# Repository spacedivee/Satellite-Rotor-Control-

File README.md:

## *$FOR THE STARDANCE REVIEWERS$*
- In case you haven't read it through my comments already , my BOM.csv is irrelevant if you guys can **ship me a HackPad kit** +(the PCB grant). I need the exact same components as the components in the kit, so sending me my grant isn't necessary (Either way my BOM contains the same components bought individually (which just costs more than your bulk), so its a win-win for both of us if you ship a **HackPad kit**. Note: I would submit this project as a hackpad, but previous reviewers have been agaisnt that. Thank you for your understanding.

## Custom Satellite Control Interface
A custom PCB-based controller designed as a physical interface for controlling software on a computer. It can be used as a general-purpose control pad, with a focus on eventually controlling a **satellite antenna rotator** (which is another project I am building).

## Components and building materials.
* 4× MX-style buttons
* EC11E rotary encoder with push button
* 0.91" OLED display
* Seeed XIAO RP2040
* Custom KiCad PCB
* 3D-printed Onshape enclosure

## PCB+Circuit

## How It Works
The XIAO RP2040 reads the buttons and rotary encoder and sends their inputs to software running on a computer. The OLED provides feedback to the user. In my case, the OLED will display Azimuth and Elevation as they are being changed so the antenna adjustmenet can be simplified. The Encoder will be used to manually adjust the increment of the motors, such that each press will be greater or smaller, depending on the input. 
All of the information will then be sent to the XIAO, which will then sent it to my computer as keystroke data (my current method), which my antenna rotator software will then acknowledge. 

## Tools (if you were interested..?)

* **KiCad** — PCB design
* **Onshape** — enclosure design
* **Arduino/C++** — programming
* **JLCPCB** — PCB manufacturing

## Firmware
For the record, this is the only aspect of my project that was completely made by AI. The current firmware is a placeholder and I plan on writing it myself once I have built the board. I believe this is a better way
of doing things since I get to actively troubleshoot issues. I hope yall feel the same way about this ❤️.

## Bill of Materials

| Item | Component Name | Qty | Price (USD) | Notes |
| :---: | :--- | :---: | :---: | :--- |
| 1 | [Seeed XIAO RP2040](https://www.amazon.ca/dp/B0FB5BS2NX?psc=1&ref_=cm_sw_r_cp_ud_ct_R7M1Z3YGXBJXF9ZXZQDJ_10) | 1 | $19.32 | Main microcontroller |
| 2 | [1N4148 through-hole diodes](https://www.amazon.ca/dp/B099PPQ7YN?psc=1&ref_=cm_sw_r_cp_ud_ct_R7M1Z3YGXBJXF9ZXZQDJ_9) | 4 | $1.50 | Button/switch matrix |
| 3 | [MX-style switches](https://www.amazon.ca/dp/B0HJFQYWR2?psc=1&ref_=cm_sw_r_cp_ud_ct_R7M1Z3YGXBJXF9ZXZQDJ_8) | 4 | $5.99 | Main input buttons |
| 4 | [EC11E rotary encoder with switch](https://www.amazon.ca/dp/B0GJS5SQPF?psc=1&ref_=cm_sw_r_cp_ud_ct_R7M1Z3YGXBJXF9ZXZQDJ_7) | 1 | $8.79 | - |
| 5 | [0.91 inch OLED display](https://www.amazon.ca/dp/B0GWPY5LMY?psc=1&ref_=cm_sw_r_cp_ud_ct_R7M1Z3YGXBJXF9ZXZQDJ_5) | 1 | $6.67 | GND-VCC-SCL-SDA pin order |
| 6 | [White blank DSA keycaps](https://www.amazon.ca/dp/B0BWDR7LQQ?psc=1&ref_=cm_sw_r_cp_ud_ct_R7M1Z3YGXBJXF9ZXZQDJ_4) | 4 | $12.50 | Keycaps for MX switches |
| 7 | [M3x16mm screws](https://www.amazon.ca/dp/B0DDNJXLF3?psc=1&ref_=cm_sw_r_cp_ud_ct_R7M1Z3YGXBJXF9ZXZQDJ_3) | 4 | $8.59 | Case assembly |
| 8 | [M3x5mmx4mm heat-set inserts](https://www.amazon.ca/dp/B0BYVLPG4R?psc=1&ref_=cm_sw_r_cp_ud_ct_R7M1Z3YGXBJXF9ZXZQDJ_1) | 4 | $8.49 | Case assembly |
| 9 | $10 JLCPCB credit | 1 | $10.00 | PCB manufacturing |
| 10 | LED | 1 | $0.00 | - supplied by me |
| 11 | Resistor | 1 | $0.00 | - supplied by me |
| 12 | Shipping | 1 | $4.20 |
| | **Total Estimated Cost:** | | **$86.05** | |

> **Note:** If you have an existing hackpad kit available, I would happily accept that as an alternative. It may be more cost-effective and prevents acquiring unnecessary duplicate components.

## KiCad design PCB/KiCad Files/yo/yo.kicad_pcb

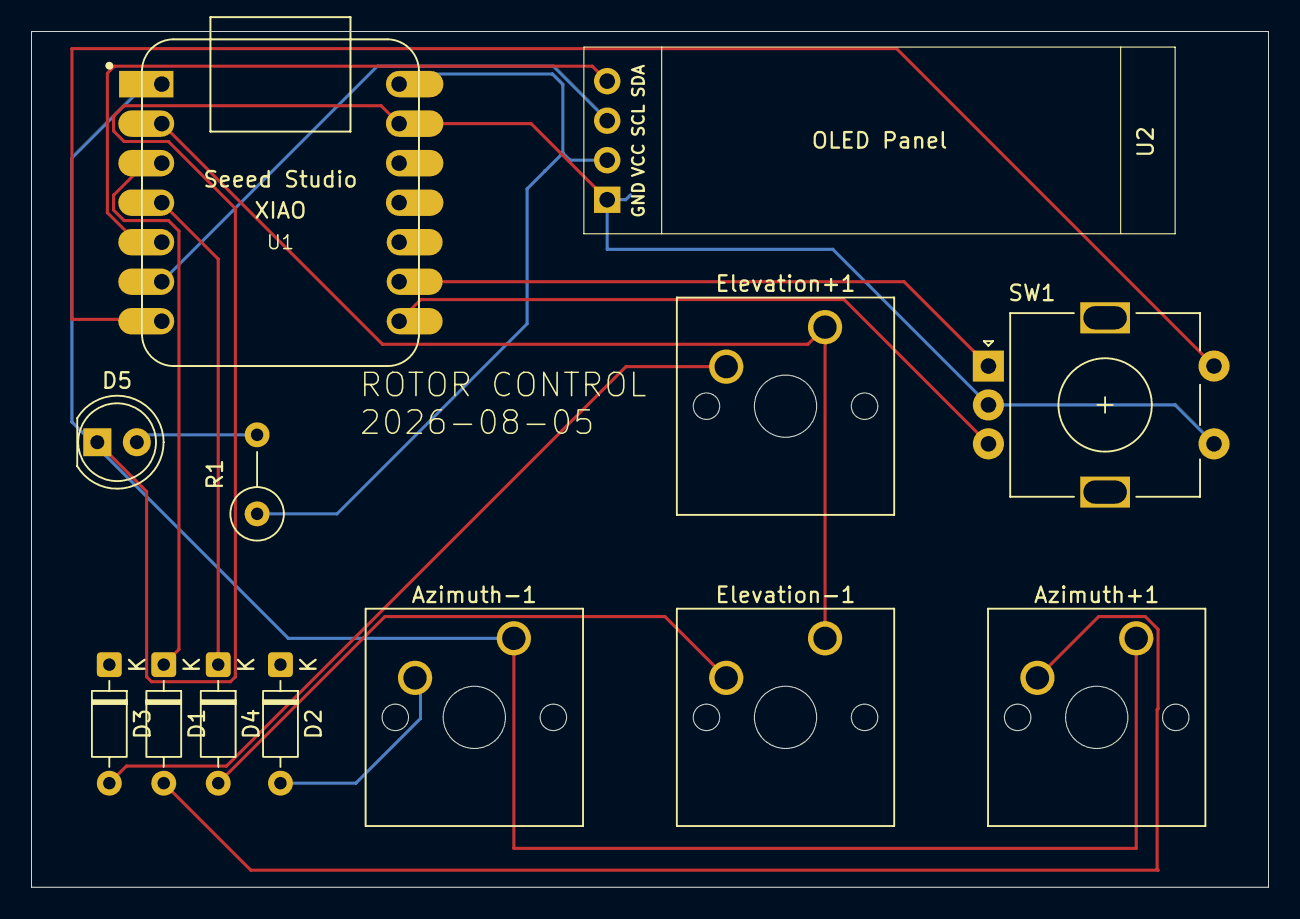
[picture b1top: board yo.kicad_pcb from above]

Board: 2 copper layers, 79.5 x 55.0 mm, 13 parts (0 on the bottom side), 16 nets.

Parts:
Azimuth+1: SW_Push; SW_Cherry_MX_1.00u_PCB
Azimuth-1: SW_Push; SW_Cherry_MX_1.00u_PCB
D1, D2, D3, D4: 1N4148; D_DO-35_SOD27_P7.62mm_Horizontal
D5: LED; LED_D5.0mm
Elevation+1: SW_Push; SW_Cherry_MX_1.00u_PCB
Elevation-1: SW_Push; SW_Cherry_MX_1.00u_PCB
R1: R; R_Axial_DIN0309_L9.0mm_D3.2mm_P5.08mm_Vertical
SW1: RotaryEncoder_Switch; RotaryEncoder_Alps_EC11E-Switch_Vertical_H20mm
U1: MOUDLE-SEEEDUINO-XIAO; XIAO-Generic-Hybrid-14P-2.54-21X17.8MM
U2: ER_OLEDM0.91_1x-I2C; SSD1306-0.91-OLED-4pin-128x32

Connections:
GND: D5.1 (K), SW1.C, SW1.S1, U1.13 (GND), U2.1 (GND)
unnamed: Azimuth+1.2, D1.2 (A)
unnamed: D1.1 (K), D3.1 (K), U1.3 (PA10_A2_D2)
unnamed: Azimuth-1.2, D2.2 (A)
unnamed: D2.1 (K), D4.1 (K), U1.4 (PA11_A3_D3)
unnamed: D3.2 (A), Elevation+1.2
unnamed: D4.2 (A), Elevation-1.2
unnamed: D5.2 (A), R1.2
unnamed: R1.1, U1.14 (5V), U2.2 (VCC)
unnamed: Azimuth+1.1, Azimuth-1.1, U1.1 (PA02_A0_D0)
unnamed: Elevation+1.1, Elevation-1.1, U1.2 (PA4_A1_D1)
unnamed: SW1.A, U1.9 (PA7_A8_D8_SCK)
unnamed: U1.5 (PA8_A4_D4_SDA), U2.4 (SDA)
unnamed: U1.6 (PA9_A5_D5_SCL), U2.3 (SCL)
unnamed: SW1.S2, U1.7 (PB08_A6_D6_TX)
unnamed: SW1.B, U1.8 (PB09_A7_D7_RX)
